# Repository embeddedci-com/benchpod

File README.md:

# BenchPod

**NOTE1: Some tagged versions will have obvious mistakes in them, but as those got built, they're in the repo for historical reasons.**

**NOTE2: Don't build these boards yourself without any necessary changes. The current tagged versions are not production-ready yet.**

**An open hardware bench tool with sensor sim, CAN, analog I/O, and power control, with a Python SDK and pytest integration.**

Embedded teams often end up with a bench full of equipment that's hard to share, hard to automate, and difficult to use remotely. Setting up tests often means being physically present, and that doesn't scale well across a team.

BenchPod is an attempt to make that easier. One board with sensor simulation over I2C and SPI, CAN bus, analog input and output, programmable power control, a logic analyzer, and an FPGA for fast protocol mocking, connected over WiFi so it can be shared across a team or accessed remotely. A Python SDK and pytest integration make it straightforward to go from manual bench work to automated tests without changing your setup.

This repo contains the KiCad source files for the board, plus the SPICE simulations used while designing the analog front ends.

---

## What's in this repo

```
pcb/
  benchpod/                      # KiCad project for the analog + digital board
    vbench-pod.kicad_pro         #   KiCad project file
    vbench-pod.kicad_pcb         #   PCB layout
    vbench-pod.kicad_sch         #   Top-level schematic
    analog-power-v2.kicad_sch    #   Analog supply rails
    analog-switching.kicad_sch   #   Analog signal routing / muxing
    analog-to-digital-v2.kicad_sch  # ADC front end
    digital-to-analog-v2.kicad_sch  # DAC output stage
    LogicAnalyzer.kicad_sch      #   Logic analyzer
    power.kicad_sch              #   Power control
    ethernet.kicad_sch           #   Ethernet
    usb.kicad_sch                #   USB
    fp-lib-table                 #   Footprint library references
    sym-lib-table                #   Symbol library references
  benchpod-digital/              # KiCad project for the digital-only board (same sheet layout)
  libs/                          # Shared symbol, footprint, and 3D-model libraries

spice/                           # LTspice / ngspice simulations for the analog front ends
  adc-v1/  adc-v2/  dac-v2/
```

Library paths in `fp-lib-table`, `sym-lib-table`, and the PCB are stored relative to
the project (`${KIPRJMOD}/..`), so the project opens in KiCad straight after cloning.

---

## Which board do I have?

The board name is printed on the silkscreen (for example "BenchPod v3-r1"). Find it in the table
below to get the git tag with the exact design files for your board:

| Silkscreen | Board | Tag | KiCad project | What changed |
|---|---|---|---|---|
| BenchPod v3 | Analog + digital | `analog-v3` | `pcb/benchpod` | First v3 board. STM32H563ZIT6, INA238 current monitors. |
| BenchPod v3-Digital | Digital only | `digital-v3` | `pcb/benchpod-digital` | First digital-only board: the v3 without the analog section. STM32H563ZGT6 (1 MB flash), INA226 current monitors. |
| BenchPod v3-r1 | Analog + digital | `analog-v3r1` | `pcb/benchpod` | STM32H563ZGT6 and INA226 like the digital board. Monitors the pod's own current (INA226 at 0x41). The 5.5 V analog rail comes from a 7 V boost instead of the 14 V rail, so U50 no longer runs hot. TPS65131 compensation caps fixed. THS4551 and TPS7A2050 in their smaller packages (RUN, DQN). |
| BenchPod v3r2-Digital | Digital only | `digital-v3r2` | `pcb/benchpod-digital` | Monitors the pod's own current (INA226 at 0x41). |
| BenchPod v3-r2 | Analog + digital | `analog-v3r2` | `pcb/benchpod` | One DAC8554 quad DAC (a channel per output) replaces the DAC8551 and its two TMUX1104 muxes. The ±14 V supply starts off and the firmware switches it on. 0.1 % resistors around the ADC driver for a smaller zero offset between pods. Fixed 9.1 pF ADC compensation instead of the trimmer. SWD and USART2 on DNP 2x2 headers instead of H1-H3. More ESD clamps (USB CC, +1V8, LA_VCCIO, the 0-5 V SMA). Board revision strap 2.70 V. |
| BenchPod v3r3-Digital | Digital only | `digital-v3r3` | `pcb/benchpod-digital` | 24-pin FFC connector (CN1) for the analog module. The module 5 V and the USB-A bridge 5 V are switched by SY6280AAC power switches, with TVS diodes on the 5 V outputs. 3.3 V buck becomes a TPS62130A with a 2.2 uH inductor. PSRAM in SOP-8. Ethernet EMI changes from the Microchip and TI reference designs: RJ45 chassis ground straight to GND, center taps fed through a 0 ohm resistor, 8.2 pF on the four data lines, a flow-through TPD4E05U06 ESD clamp. 100 nF + 470 pF at the J4, J5 and J6 terminals. Connectors placed for the enclosure. |
| BenchPod v3-r3-analog | Analog module | `analog-v3r3` | `pcb/benchpod-analog` | First analog module: the analog section on its own board, connected to the v3r3 digital board by a 24-pin FFC (CN1). Front-panel connectors for the enclosure: a lead-free BNC for the ADC input (ready for 10x probes), pluggable terminal blocks for the DAC outputs (one 6-pin block) and the 4-20 mA loop. Module ID EEPROM. +3V3 from an AP2112K-3.3. |

To get the files for your board, check out its tag:

```
git checkout analog-v3r1
```

Every tag holds all KiCad projects; use the folder from the table. Older boards: `v1.0.0` and
`v1.0.1` are v1, `v2.0.0` is v2.

The v3 tags used to be named `v3.0.0` (now `analog-v3`), `v3.0.1-digital` (now `digital-v3`),
`v3.0.1-analog` (now `analog-v3r1`) and `v3.0.2-digital` (now `digital-v3r2`).

One firmware runs on all v3 boards. The pod's own current needs firmware newer than 3.5.1.
The v3-r2 board needs firmware newer than 3.9.4: older firmware runs it as a v3-r1 and its DAC
outputs and ±12 V stay off.

---

## License

Hardware (schematics, PCB layout) is released under [CERN OHL-W v2](https://ohwr.org/cern_ohl_w_v2.txt).

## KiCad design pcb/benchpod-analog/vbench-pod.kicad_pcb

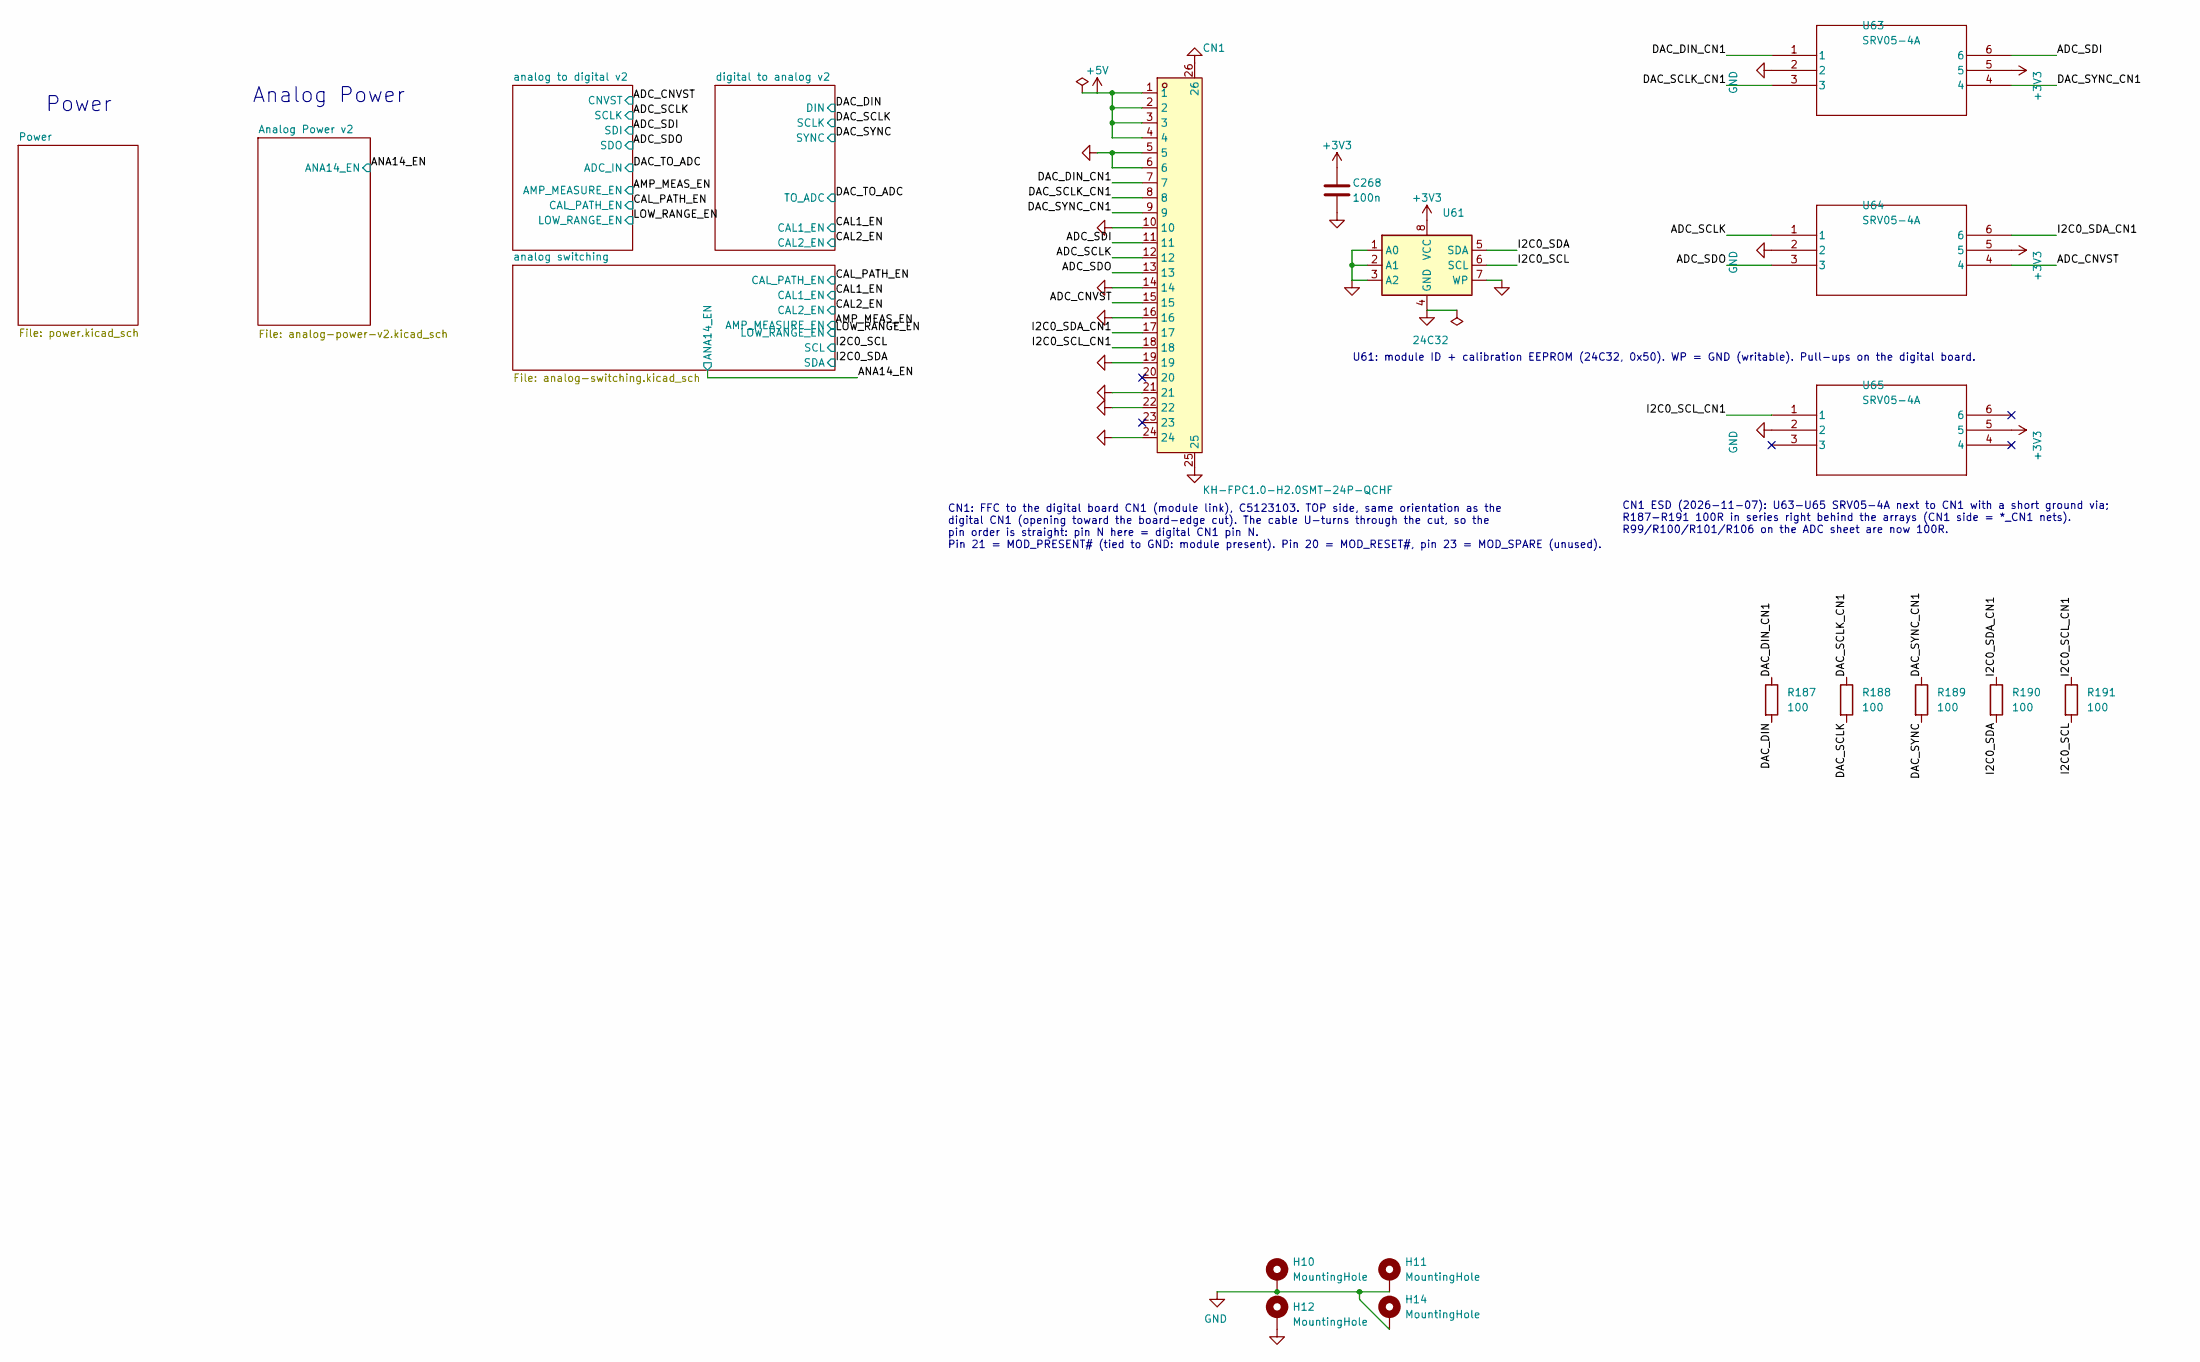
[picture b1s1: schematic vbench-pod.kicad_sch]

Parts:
C268: 100n; C_0402_1005Metric; LCSC C307331
CN1: KH-FPC1.0-H2.0SMT-24P-QCHF; C5123103_FPC-SMD_24P-P1.00_KH-FPC1.0-H2.0SMT-24P-QCHF; LCSC C5123103
H10, H11, H12, H14: MountingHole; MountingHole_2.7mm_M2.5_Pad_Via
R187, R188, R189, R190, R191: 100; R_0402_1005Metric; LCSC C25076
U61: 24C32; C18723546_SOP-8_L4.9-W3.9-P1.27-LS6.0-BL; LCSC C18723546
U63, U64, U65: SRV05-4A; SOT-23-6_L2.9-W1.6-P0.95-LS2.8-BR; LCSC C20615829

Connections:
+3V3: C268.1, U61.8 (VCC), U63.5, U64.5, U65.5; also elsewhere on the board
+5V: CN1.1, CN1.2, CN1.3, CN1.4; also elsewhere on the board
/ADC_CNVST: CN1.15, U64.4; also elsewhere on the board
/ADC_SCLK: CN1.12, U64.1; also elsewhere on the board
/ADC_SDI: CN1.11, U63.6; also elsewhere on the board
/ADC_SDO: CN1.13, U64.3; also elsewhere on the board
/DAC_DIN: CN1.7, R187.1, U63.1; also elsewhere on the board
/DAC_SCLK: CN1.8, R188.1, U63.3; also elsewhere on the board
/DAC_SYNC: CN1.9, R189.1, U63.4; also elsewhere on the board
/I2C0_SCL: CN1.18, R191.1, R191.2, U61.6 (SCL), U65.1; also elsewhere on the board
/I2C0_SDA: CN1.17, R190.1, R190.2, U61.5 (SDA), U64.6; also elsewhere on the board
GND: C268.2, CN1.5, CN1.6, CN1.10, CN1.14, CN1.16, CN1.19, CN1.21, CN1.22, CN1.24, CN1.25, CN1.26, H10.1 (1_1), H11.1 (1_1), H12.1 (1_1), H14.1 (1_1), U61.1 (A0), U61.2 (A1), U61.3 (A2), U61.4 (GND), U61.7 (WP), U63.2, U64.2, U65.2; also elsewhere on the board

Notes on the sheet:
Analog Power
CN1: FFC to the digital board CN1 (module link), C5123103. TOP side, same orientation as the digital CN1 (opening toward the board-edge cut). The cable U-turns through the cut, so the pin order is straight: pin N here = digital CN1 pin N. Pin 21 = MOD_PRESENT# (tied to GND: module present). Pin 20 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
U61: module ID + calibration EEPROM (24C32, 0x50). WP = GND (writable). Pull-ups on the digital board.
Power
CN1 ESD (2026-11-07): U63-U65 SRV05-4A next to CN1 with a short ground via; R187-R191 100R in series right behind the arrays (CN1 side = *_CN1 nets). R99/R100/R101/R106 on the ADC sheet are now 100R.

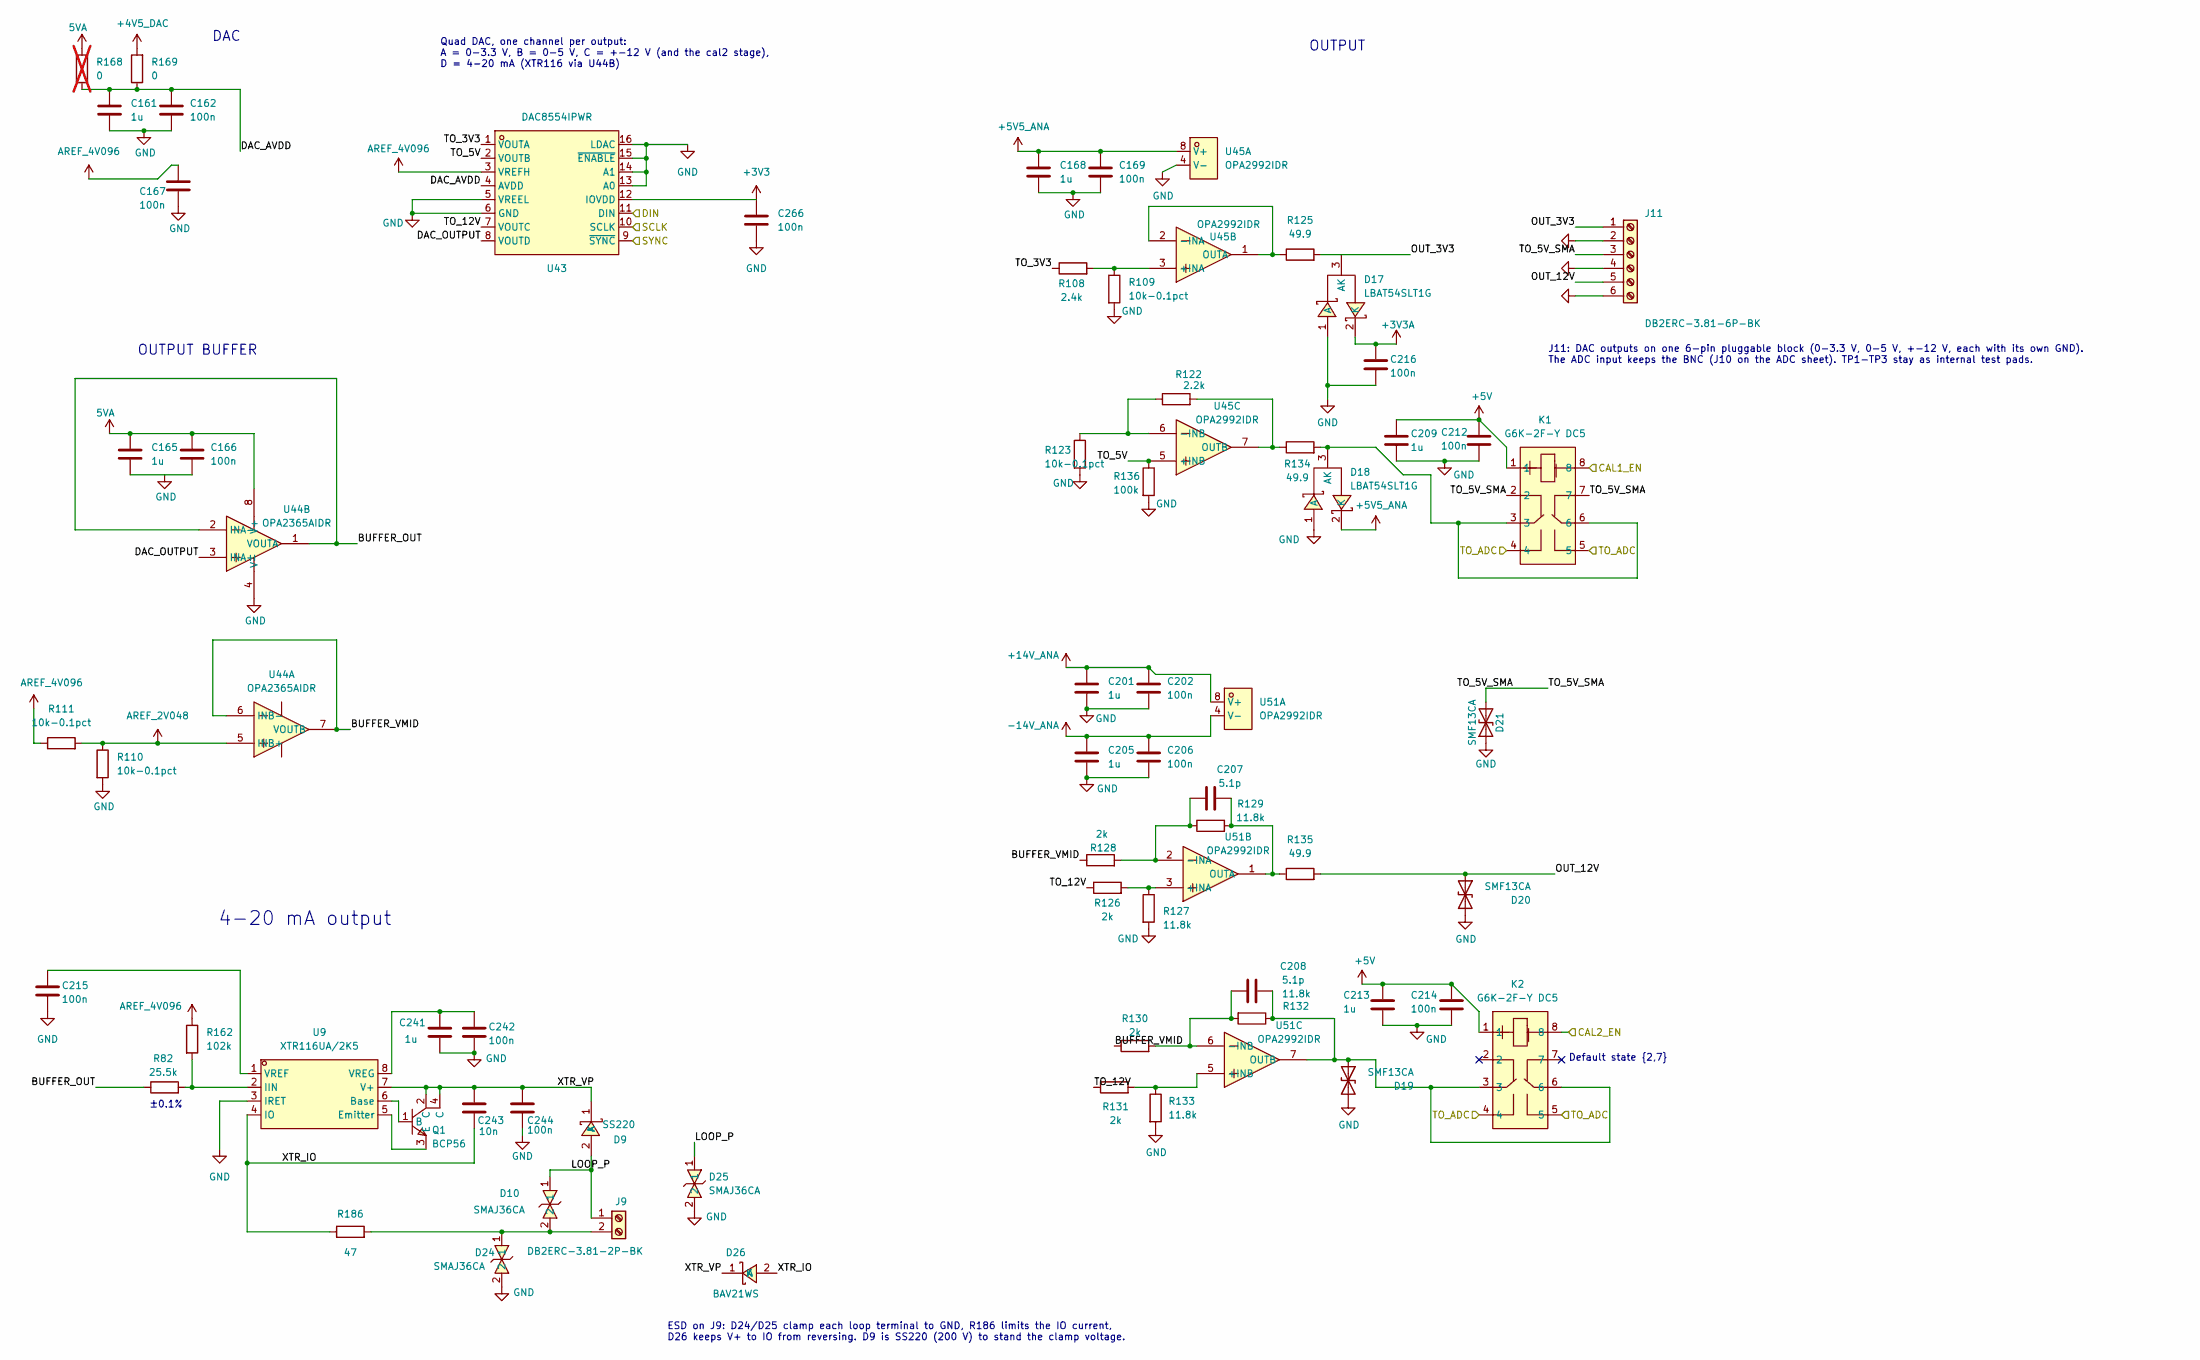
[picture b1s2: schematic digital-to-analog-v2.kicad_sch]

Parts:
C161, C201, C205, C241: 1u; C_0402_1005Metric; MPN GRM155R61H105KE05D; LCSC C1518208
C162, C166, C167, C169, C202, C206, C212, C214, C215, C216, C242, C244: 100n; C_0402_1005Metric; MPN CC0603KRX7R9BB104; LCSC C307331
C165, C168, C209, C213: 1u; C_0402_1005Metric; MPN CL05A105KA5NQNC; LCSC C52923
C207, C208: 5.1p; C_0603_1608Metric; LCSC C20617868
C243: 10n; C_0402_1005Metric; LCSC C15195
C266: 100n; C_0402_1005Metric; LCSC C307331
D9: SS220; SMA_L4.3-W2.6-LS5.2-RD; MPN SS220; LCSC Part C7420361
D10, D24, D25: SMAJ36CA; SMA_L4.3-W2.6-LS5.0-BI; MPN SMAJ36CA; LCSC Part C5353135
D17, D18: LBAT54SLT1G; SOT-23_L2.9-W1.3-P1.90-LS2.4-BR; MPN LBAT54SLT1G; LCSC Part C12765
D19, D20: SMF13CA; SOD-123FL_L3.0-W1.8-LS3.7-BI; MPN SMF13CA; LCSC Part C1851355
D21: SMF13CA; SOD-123FL_L3.0-W1.8-LS3.7-BI; MPN SMF13CA; LCSC C1851355
D26: BAV21WS; D_SOD-323; MPN BAV21WS; LCSC Part C7420334
J9: DB2ERC-3.81-2P-BK; C5259145_CONN-TH_2P-P3.81_DB2ERC-3.81-2P-BK; MFR. Part # DB2ERC-3.81-2P-BK; LCSC Part # C5259145
J11: DB2ERC-3.81-6P-BK; C5244107_HDR-TH_DB2ERC-3.81-6P-BK; LCSC C5244107
K1, K2: G6K-2F-Y DC5; RELAY-TH_G6K-2F-Y; MPN G6K-2F-Y-TR DC5 BY OMR/C; LCSC Part C231390
Q1: BCP56; SOT-223-4_L6.5-W3.5-P2.30-LS7.0-BR; MPN BCP56; LCSC C5345976
R82: 25.5k; R_0603_1608Metric; LCSC C861257
R108: 2.4k; R_0603_1608Metric; LCSC C861300
R109, R110, R111, R123: 10k-0.1pct; R_0402_1005Metric; LCSC C190095
R122: 2.2k; R_0402_1005Metric; LCSC C326602
R125, R134, R135: 49.9; R_0402_1005Metric; LCSC C325388
R126, R128, R130, R131: 2k; R_0402_1005Metric; LCSC C852711
R127, R129, R132, R133: 11.8k; R_0402_1005Metric; LCSC C852496
R136: 100k; R_0402_1005Metric; LCSC C25741
R162: 102k; R_0603_1608Metric; LCSC C861068
R168: 0; R_0402_1005Metric; LCSC C17168; not fitted
R169: 0; R_0402_1005Metric; LCSC C17168
R186: 47; R_0603_1608Metric; LCSC C23182
U9: XTR116UA/2K5; SOIC-8_L5.0-W4.0-P1.27-LS6.0-BL; MPN XTR116UA/2K5; LCSC Part C368611
U43: DAC8554IPWR; C527522_TSSOP-16_L5_0-W4_4-P0_65-LS6_4-BL; MPN DAC8554IPWR; LCSC C527522
U44: OPA2365AIDR; SOIC-8_L4.9-W3.9-P1.27-LS6.0-BL; MPN OPA2365AIDR; LCSC Part C130011
U45, U51: OPA2992IDR; SOIC-8_L4.9-W3.9-P1.27-LS6.0-BL; MPN OPA2992IDR; LCSC Part C4368953

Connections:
5VA: C165.2, C166.2, R168.2, U44.8 (V+); also elsewhere on the board
+3V3: C266.1, U43.12 (IOVDD); also elsewhere on the board
+3V3A: C216.2, D17.2 (K); also elsewhere on the board
+4V5_DAC: R169.2; also elsewhere on the board
+5V: C209.2, C212.2, C213.2, C214.2, K1.1, K2.1; also elsewhere on the board
+5V5_ANA: C168.2, C169.2, D18.2 (K), U45.8 (V+); also elsewhere on the board
+14V_ANA: C201.2, C202.2, U51.8 (V+); also elsewhere on the board
-14V_ANA: C205.2, C206.2, U51.4 (V-); also elsewhere on the board
/CAL1_EN: K1.8; also elsewhere on the board
/CAL2_EN: K2.8; also elsewhere on the board
/DAC_DIN: U43.11 (DIN); also elsewhere on the board
/DAC_SCLK: U43.10 (SCLK); also elsewhere on the board
/DAC_SYNC: U43.9 (~SYNC); also elsewhere on the board
/DAC_TO_ADC: K1.4, K1.5, K2.4, K2.5; also elsewhere on the board
/digital to analog v2/BUFFER_OUT: R82.1, U44.1 (VOUTA), U44.2 (INA-)
/digital to analog v2/BUFFER_VMID: R128.1, R130.1, U44.6 (INB-), U44.7 (VOUTB)
/digital to analog v2/DAC_AVDD: C161.2, C162.2, R168.1, R169.1, U43.4 (AVDD)
/digital to analog v2/DAC_OUTPUT: U43.8 (VOUTD), U44.3 (INA+)
/digital to analog v2/OUT_3V3: D17.3 (AK), J11.1, R125.2
/digital to analog v2/OUT_12V: D20.1 (A1), J11.5, R135.2
/digital to analog v2/TO_3V3: R108.1, U43.1 (VOUTA)
/digital to analog v2/TO_5V: R136.1, U43.2 (VOUTB), U45.5 (+INB)
/digital to analog v2/TO_5V_SMA: D21.2 (A2), J11.3, K1.2, K1.7
/digital to analog v2/TO_12V: R126.1, R131.1, U43.7 (VOUTC)
AREF_2V048: R110.1, R111.2, U44.5 (INB+)
AREF_4V096: C167.2, R111.1, R162.1, U43.3 (VREFH); also elsewhere on the board
GND: C161.1, C162.1, C165.1, C166.1, C167.1, C168.1, C169.1, C201.1, C202.1, C205.1, C206.1, C209.1, C212.1, C213.1, C214.1, C215.1, C216.1, C241.1, C242.1, C244.1, C266.2, D17.1 (A), D18.1 (A), D19.2 (A2), D20.2 (A2), D21.1 (A1), D24.2, D25.2, J11.2, J11.4, J11.6, R109.2, R110.2, R123.2, R127.2, R133.2, R136.2, U9.3 (IRET), U43.5 (VREEL), U43.6 (GND), U43.13 (A0), U43.14 (A1), U43.15 (~ENABLE), U43.16 (LDAC), U44.4 (V-), U45.4 (V-); also elsewhere on the board
unnamed: D9.2 (A), D10.1, D25.1, J9.1
unnamed: C243.1, C244.2, D9.1 (K), D26.1 (K), Q1.2 (C), Q1.4 (C), U9.7 (V+)
unnamed: D18.3 (AK), K1.3, K1.6, R134.2
unnamed: C208.2, D19.1 (A1), K2.3, K2.6, R132.1, U51.7 (OUTB)
unnamed: Q1.1 (B), U9.6 (Base)
unnamed: Q1.3 (E), U9.5 (Emitter)
unnamed: R82.2, R162.2, U9.2 (IIN)
unnamed: C215.2, U9.1 (VREF)
unnamed: C241.2, C242.2, U9.8 (VREG)
unnamed: R108.2, R109.1, U45.3 (+INA)
unnamed: R125.1, U45.1 (OUTA), U45.2 (-INA)
unnamed: R122.1, R123.1, U45.6 (-INB)
unnamed: R122.2, R134.1, U45.7 (OUTB)
unnamed: R126.2, R127.1, U51.3 (+INA)
unnamed: C207.1, R128.2, R129.1, U51.2 (-INA)
unnamed: C207.2, R129.2, R135.1, U51.1 (OUTA)
unnamed: R131.2, R133.1, U51.5 (+INB)
unnamed: C208.1, R130.2, R132.2, U51.6 (-INB)

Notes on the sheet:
Default state {2,7}
J11: DAC outputs on one 6-pin pluggable block (0-3.3 V, 0-5 V, +-12 V, each with its own GND). The ADC input keeps the BNC (J10 on the ADC sheet). TP1-TP3 stay as internal test pads.
±0.1%
OUTPUT BUFFER
OUTPUT
Quad DAC, one channel per output: A = 0-3.3 V, B = 0-5 V, C = +-12 V (and the cal2 stage), D = 4-20 mA (XTR116 via U44B)
DAC
4-20 mA output
ESD on J9: D24/D25 clamp each loop terminal to GND, R186 limits the IO current, D26 keeps V+ to IO from reversing. D9 is SS220 (200 V) to stand the clamp voltage.

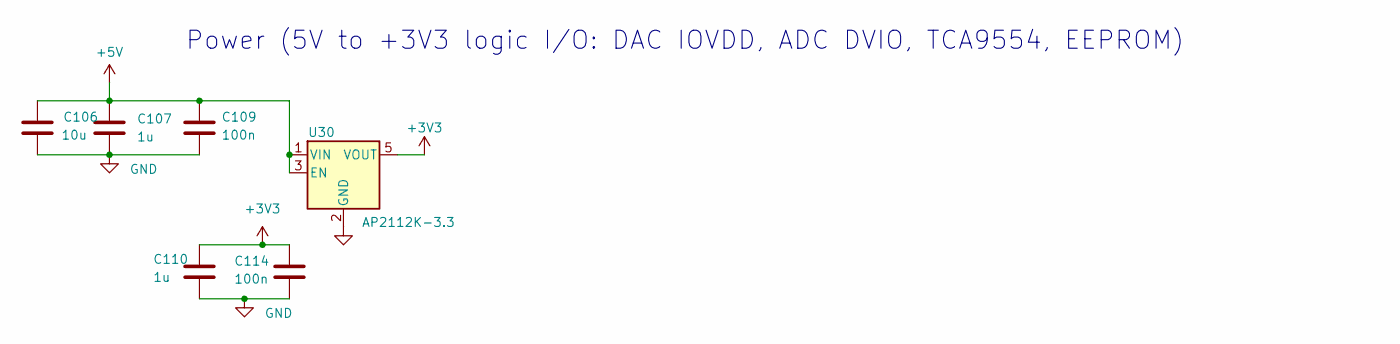
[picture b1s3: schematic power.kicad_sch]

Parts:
C106: 10u; C_0603_1608Metric; LCSC C96446
C107: 1u; C_0402_1005Metric; MPN CL05A105KA5NQNC; LCSC C52923
C109, C114: 100n; C_0402_1005Metric; MPN CC0603KRX7R9BB104; LCSC C307331
C110: 1u; C_0402_1005Metric; MPN GRM155R61H105KE05D; LCSC C1518208
U30: AP2112K-3.3; SOT-25-5_L2.9-W1.6-P0.95-LS2.8-BL; LCSC C51118

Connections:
+3V3: C110.2, C114.2, U30.5 (VOUT); also elsewhere on the board
+5V: C106.2, C107.2, C109.2, U30.1 (VIN), U30.3 (EN); also elsewhere on the board
GND: C106.1, C107.1, C109.1, C110.1, C114.1, U30.2 (GND); also elsewhere on the board

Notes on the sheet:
Power (5V to +3V3 logic I/O: DAC IOVDD, ADC DVIO, TCA9554, EEPROM)

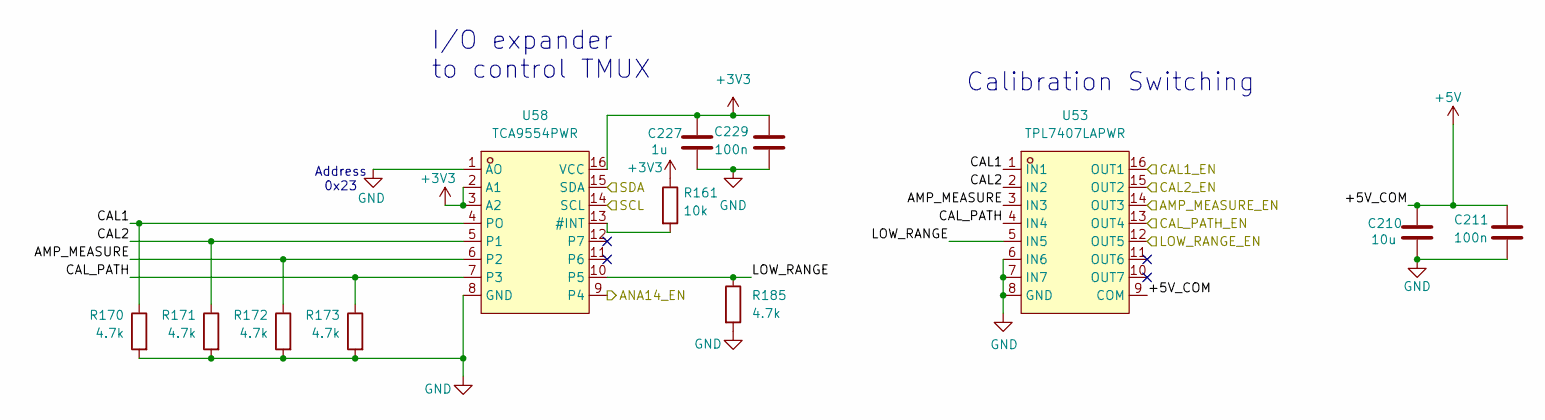
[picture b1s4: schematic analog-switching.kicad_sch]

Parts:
C210: 10u; C_0603_1608Metric; MPN CL21B105KBFNNNE; LCSC C96446
C211: 100n; C_0402_1005Metric; MPN CC0603KRX7R9BB104; LCSC C307331
C227: 1u; C_0402_1005Metric; MPN GRM155R61H105KE05D; LCSC C1518208
C229: 100n; C_0402_1005Metric; LCSC C307331
R161: 10k; R_0402_1005Metric; LCSC C25744
R170, R171, R172, R173, R185: 4.7k; R_0402_1005Metric; LCSC C25900
U53: TPL7407LAPWR; TSSOP-16_L5.0-W4.4-P0.65-LS6.4-BL; MPN TPL7407LAPWR; LCSC Part C2149827
U58: TCA9554PWR; TSSOP-16_L5.0-W4.4-P0.65-LS6.4-TL; MPN TCA9554PWR; LCSC Part C477924

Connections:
+3V3: C227.2, C229.1, R161.1, U58.2 (A1), U58.3 (A2), U58.16 (VCC); also elsewhere on the board
+5V: C210.2, C211.2, U53.9 (COM); also elsewhere on the board
/AMP_MEAS_EN: U53.14 (OUT3); also elsewhere on the board
/ANA14_EN: U58.9 (P4); also elsewhere on the board
/CAL1_EN: U53.16 (OUT1); also elsewhere on the board
/CAL2_EN: U53.15 (OUT2); also elsewhere on the board
/CAL_PATH_EN: U53.13 (OUT4); also elsewhere on the board
/I2C0_SCL: U58.14 (SCL); also elsewhere on the board
/I2C0_SDA: U58.15 (SDA); also elsewhere on the board
/LOW_RANGE_EN: U53.12 (OUT5); also elsewhere on the board
/analog switching/AMP_MEASURE: R172.1, U53.3 (IN3), U58.6 (P2)
/analog switching/CAL1: R170.1, U53.1 (IN1), U58.4 (PO)
/analog switching/CAL2: R171.1, U53.2 (IN2), U58.5 (P1)
/analog switching/CAL_PATH: R173.1, U53.4 (IN4), U58.7 (P3)
/analog switching/LOW_RANGE: R185.1, U53.5 (IN5), U58.10 (P5)
GND: C210.1, C211.1, C227.1, C229.2, R170.2, R171.2, R172.2, R173.2, R185.2, U53.6 (IN6), U53.7 (IN7), U53.8 (GND), U58.1 (AO), U58.8 (GND); also elsewhere on the board
unnamed: R161.2, U58.13 (#INT)

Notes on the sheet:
I/O expander to control TMUX
Calibration Switching
Address 0x23

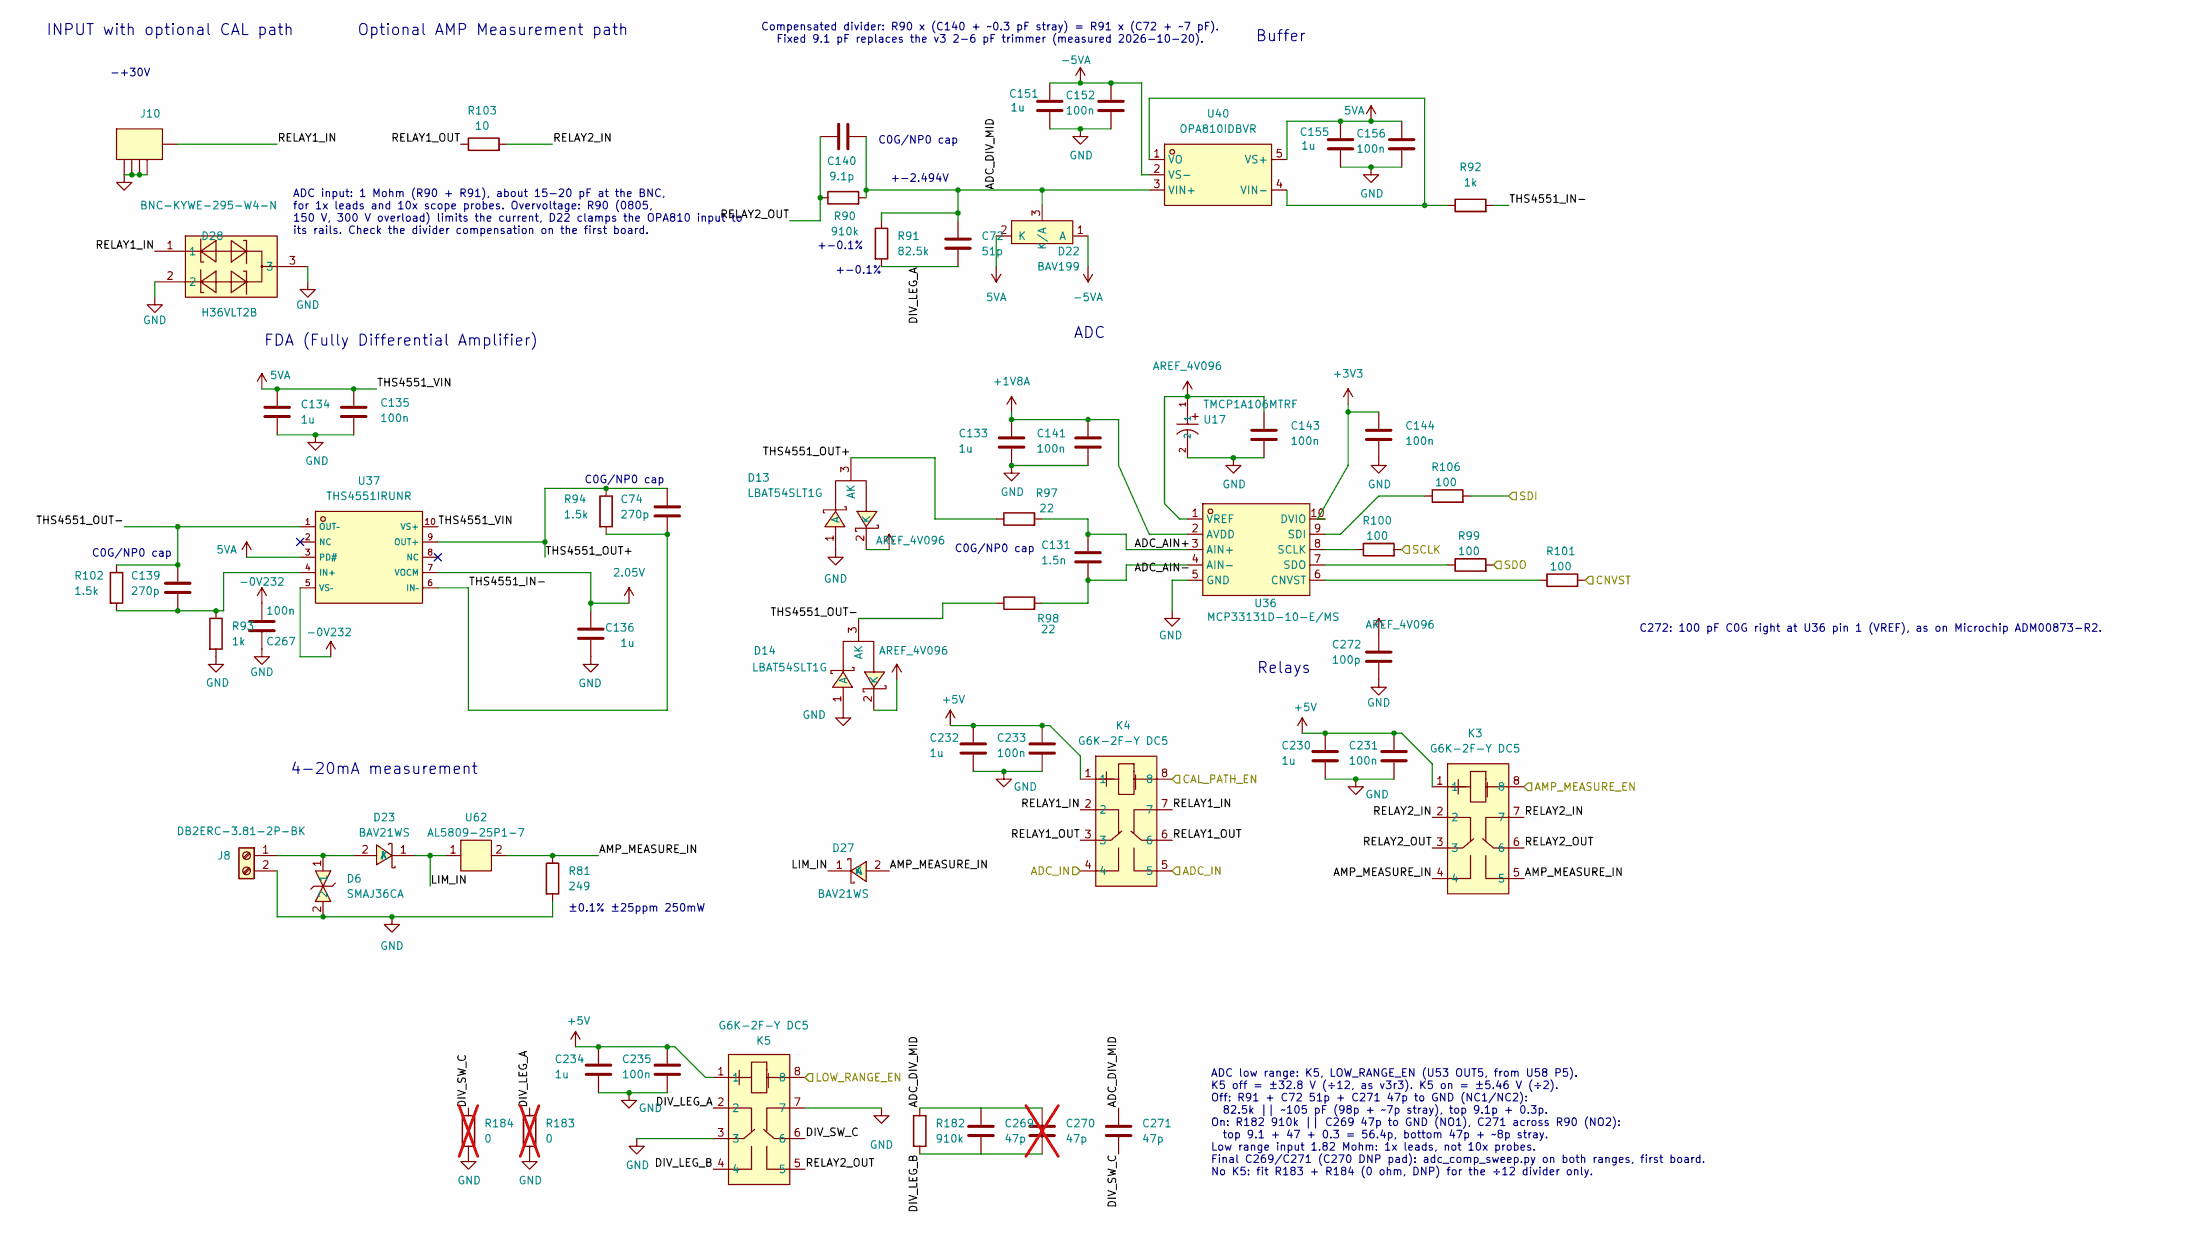
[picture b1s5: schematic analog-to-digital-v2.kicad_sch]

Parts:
C72: 51p; C_0402_1005Metric; LCSC C541437
C74, C139: 270p; C_0402_1005Metric; LCSC C161545
C131: 1.5n; C_0402_1005Metric; LCSC C668348
C133, C136: 1u; C_0402_1005Metric; MPN GRM155R61H105KE05D; LCSC C1518208
C134, C151, C155, C230, C232, C234: 1u; C_0402_1005Metric; MPN CL05A105KA5NQNC; LCSC C52923
C135, C141, C143, C144, C152, C156, C231, C233, C235: 100n; C_0402_1005Metric; MPN CC0603KRX7R9BB104; LCSC C307331
C140: 9.1p; C_0603_1608Metric; MPN GQM1875C2E9R1BB12D; LCSC C2299929
C267: 100n; C_0402_1005Metric; LCSC C307331
C269: 47p; C_0402_1005Metric; LCSC C277503
C270: 47p; C_0402_1005Metric; LCSC C277503; not fitted
C271: 47p; C_0603_1608Metric; LCSC C882574
C272: 100p; C_0402_1005Metric; MPN 0402CG101J500NT; LCSC C1546
D6: SMAJ36CA; SMA_L4.3-W2.6-LS5.0-BI; MPN SMAJ36CA; LCSC Part C5353135
D13, D14: LBAT54SLT1G; SOT-23_L2.9-W1.3-P1.90-LS2.4-BR; MPN LBAT54SLT1G; LCSC Part C12765
D22: BAV199; C145516_SOT-23_L2.9-W1.3-P1.90-LS2.4-BR; LCSC C145516
D23, D27: BAV21WS; D_SOD-323; MPN BAV21WS; LCSC Part C7420334
D28: H36VLT2B; SOT-23; LCSC C20615828
J8: DB2ERC-3.81-2P-BK; C5259145_CONN-TH_2P-P3.81_DB2ERC-3.81-2P-BK; MFR. Part # DB2ERC-3.81-2P-BK; LCSC Part # C5259145
J10: BNC-KYWE-295-W4-N; C41416668_BNC-TH_BNC-KYWE-295-W4-N; LCSC C41416668
K3, K4, K5: G6K-2F-Y DC5; RELAY-TH_G6K-2F-Y; MPN G6K-2F-Y-TR DC5 BY OMR/C; LCSC Part C231390
R81: 249; R_1206_3216Metric; LCSC C870575
R90: 910k; R_0805_2012Metric; LCSC C865698
R91: 82.5k; R_0603_1608Metric; LCSC C705796
R92, R93: 1k; R_0402_1005Metric; LCSC C852624
R94, R102: 1.5k; R_0402_1005Metric; LCSC C281775
R97, R98: 22; R_0402_1005Metric; LCSC C25092
R99, R100, R101, R106: 100; R_0402_1005Metric; LCSC C25076
R103: 10; R_0402_1005Metric; LCSC C25077
R182: 910k; R_0603_1608Metric; LCSC C2686431
R183, R184: 0; R_0603_1608Metric; LCSC C21189; not fitted
U17: TMCP1A106MTRF; C1969735_CAP-SMD_L2_0-W1_3-FD; LCSC C1969735
U36: MCP33131D-10-E/MS; MSOP-10_L3.0-W3.0-P0.50-LS5.0-BL; MPN MCP33131D-10-E/MS; LCSC Part C635978
U37: THS4551IRUNR; C2060364_QFN-10_L2_0-W2_0-P0_50-BL; LCSC C2060364
U40: OPA810IDBVR; SOT-23-5_L2.9-W1.6-P0.95-LS2.8-TL; MPN OPA810IDBVR; LCSC Part C2833513
U62: AL5809-25P1-7; POWERDI-123_L2.7-W1.6-LS3.7-RD; MPN AL5809-25P1-7; LCSC Part C2678668

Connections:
2.05V: C136.2, U37.7 (VOCM); also elsewhere on the board
5VA: C134.2, C135.2, C155.2, C156.2, D22.2 (K), U37.3 (PD#), U37.10 (VS+), U40.5 (VS+); also elsewhere on the board
+1V8A: C133.2, C141.2, U36.2 (AVDD); also elsewhere on the board
+3V3: C144.2, U36.10 (DVIO); also elsewhere on the board
+5V: C230.2, C231.2, C232.2, C233.2, C234.2, C235.2, K3.1, K4.1, K5.1; also elsewhere on the board
-5VA: C151.2, C152.2, D22.1 (A), U40.2 (VS-); also elsewhere on the board
/ADC_CNVST: R101.2; also elsewhere on the board
/ADC_SCLK: R100.2; also elsewhere on the board
/ADC_SDI: R106.2; also elsewhere on the board
/ADC_SDO: R99.2; also elsewhere on the board
/AMP_MEAS_EN: K3.8; also elsewhere on the board
/CAL_PATH_EN: K4.8; also elsewhere on the board
/DAC_TO_ADC: K4.4, K4.5; also elsewhere on the board
/LOW_RANGE_EN: K5.8; also elsewhere on the board
/analog to digital v2/ADC_DIV_MID: C72.1, C140.2, C269.1, C270.1, C271.1, D22.3 (K/A), R90.2, R91.1, R182.1, U40.3 (VIN+)
/analog to digital v2/DIV_LEG_A: C72.2, K5.2, R91.2, R183.1
/analog to digital v2/DIV_LEG_B: C269.2, C270.2, K5.4, R182.2
/analog to digital v2/DIV_SW_C: C271.2, K5.6, R184.1
/analog to digital v2/RELAY1_IN: D28.1, J10.5 (OUT), K4.2, K4.7
/analog to digital v2/RELAY1_OUT: K4.3, K4.6, R103.1
/analog to digital v2/RELAY2_IN: K3.2, K3.7, R103.2
/analog to digital v2/RELAY2_OUT: C140.1, K3.3, K3.6, K5.5, R90.1
/analog to digital v2/THS4551_IN-: C74.2, R92.2, R94.2, U37.6 (IN–)
/analog to digital v2/THS4551_OUT+: C74.1, D13.3 (AK), R94.1, R97.1, U37.9 (OUT+)
/analog to digital v2/THS4551_OUT-: C139.1, D14.3 (AK), R98.1, R102.1, U37.1 (OUT–)
AREF_4V096: C143.2, C272.1, D13.2 (K), D14.2 (K), U17.1, U36.1 (VREF); also elsewhere on the board
GND: C133.1, C134.1, C135.1, C136.1, C141.1, C143.1, C144.1, C151.1, C152.1, C155.1, C156.1, C230.1, C231.1, C232.1, C233.1, C234.1, C235.1, C267.2, C272.2, D6.2, D13.1 (A), D14.1 (A), D28.2, D28.3, J8.2, J10.1 (GND), J10.2 (GND), J10.3 (GND), J10.4 (GND), K5.3, K5.7, R81.2, R93.2, R183.2, R184.2, U17.2, U36.5 (GND); also elsewhere on the board
unnamed: D23.1 (K), D27.1 (K), U62.1 (In)
unnamed: C131.1, R97.2, U36.3 (AIN+)
unnamed: C131.2, R98.2, U36.4 (AIN-)
unnamed: R101.1, U36.6 (CNVST)
unnamed: R100.1, U36.8 (SCLK)
unnamed: R106.1, U36.9 (SDI)
unnamed: R99.1, U36.7 (SDO)
unnamed: C139.2, R93.1, R102.2, U37.4 (IN+)
unnamed: R92.1, U40.1 (VO), U40.4 (VIN-)
−0V232: C267.1, U37.5 (VS–); also elsewhere on the board

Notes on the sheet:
C0G/NP0 cap
4-20mA measurement
+-0.1%
ADC
+-2.494V
Buffer
±0.1% ±25ppm 250mW
Optional AMP Measurement path
Relays
ADC input: 1 Mohm (R90 + R91), about 15-20 pF at the BNC, for 1x leads and 10x scope probes. Overvoltage: R90 (0805, 150 V, 300 V overload) limits the current, D22 clamps the OPA810 input to its rails. Check the divider compensation on the first board.
FDA (Fully Differential Amplifier)
INPUT with optional CAL path
-+30V
Compensated divider: R90 x (C140 + ~0.3 pF stray) = R91 x (C72 + ~7 pF). Fixed 9.1 pF replaces the v3 2-6 pF trimmer (measured 2026-10-20).
ADC low range: K5, LOW_RANGE_EN (U53 OUT5, from U58 P5). K5 off = ±32.8 V (÷12, as v3r3). K5 on = ±5.46 V (÷2). Off: R91 + C72 51p + C271 47p to GND (NC1/NC2): 82.5k || ~105 pF (98p + ~7p stray), top 9.1p + 0.3p. On: R182 910k || C269 47p to GND (NO1), C271 across R90 (NO2): top 9.1 + 47 + 0.3 = 56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
C272: 100 pF C0G right at U36 pin 1 (VREF), as on Microchip ADM00873-R2.
